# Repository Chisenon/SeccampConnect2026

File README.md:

# SeccampConnect2026
Security Camp Connect 2026

## クイックスタート（開発・書き込み手順）

開発には Docker (ビルド用) とホスト側の `espflash` (書き込み用) を使用します。
アーキテクチャの図解やコマンドの詳細は [WORKFLOW.md](WORKFLOW.md) を参照してください。

### 1. 開発用コンテナの起動
バックグラウンドでビルド用コンテナを待機させます。
```powershell
docker compose up -d
```

### 2. ビルドの実行
起動中のコンテナ内で `cargo build` を実行します。
```powershell
docker compose exec build cargo build --release
```

### 3. デバイスを「書き込みモード」にする（重要！）
ESP32-S3に書き込むには、マイコンを**ダウンロードモード**にする必要があります。

1. マイコン基板上の **BOOTボタン** を押しっぱなしにする
2. PCにUSBケーブルを接続する（接続済みの場合は、BOOTを押しながらRESETボタンを押して離す）
3. BOOTボタンを離す

### 4. ファームウェアの書き込み
割り当てられたCOMポート（例：`COM3`）を確認して書き込みます。
```powershell
# ポート確認
Get-CimInstance Win32_SerialPort | Select-Object Name, Description

# フラッシュ（COM3の場合）
espflash flash .\target\xtensa-esp32s3-none-elf\release\SeccampConnect2026 --port COM3
```

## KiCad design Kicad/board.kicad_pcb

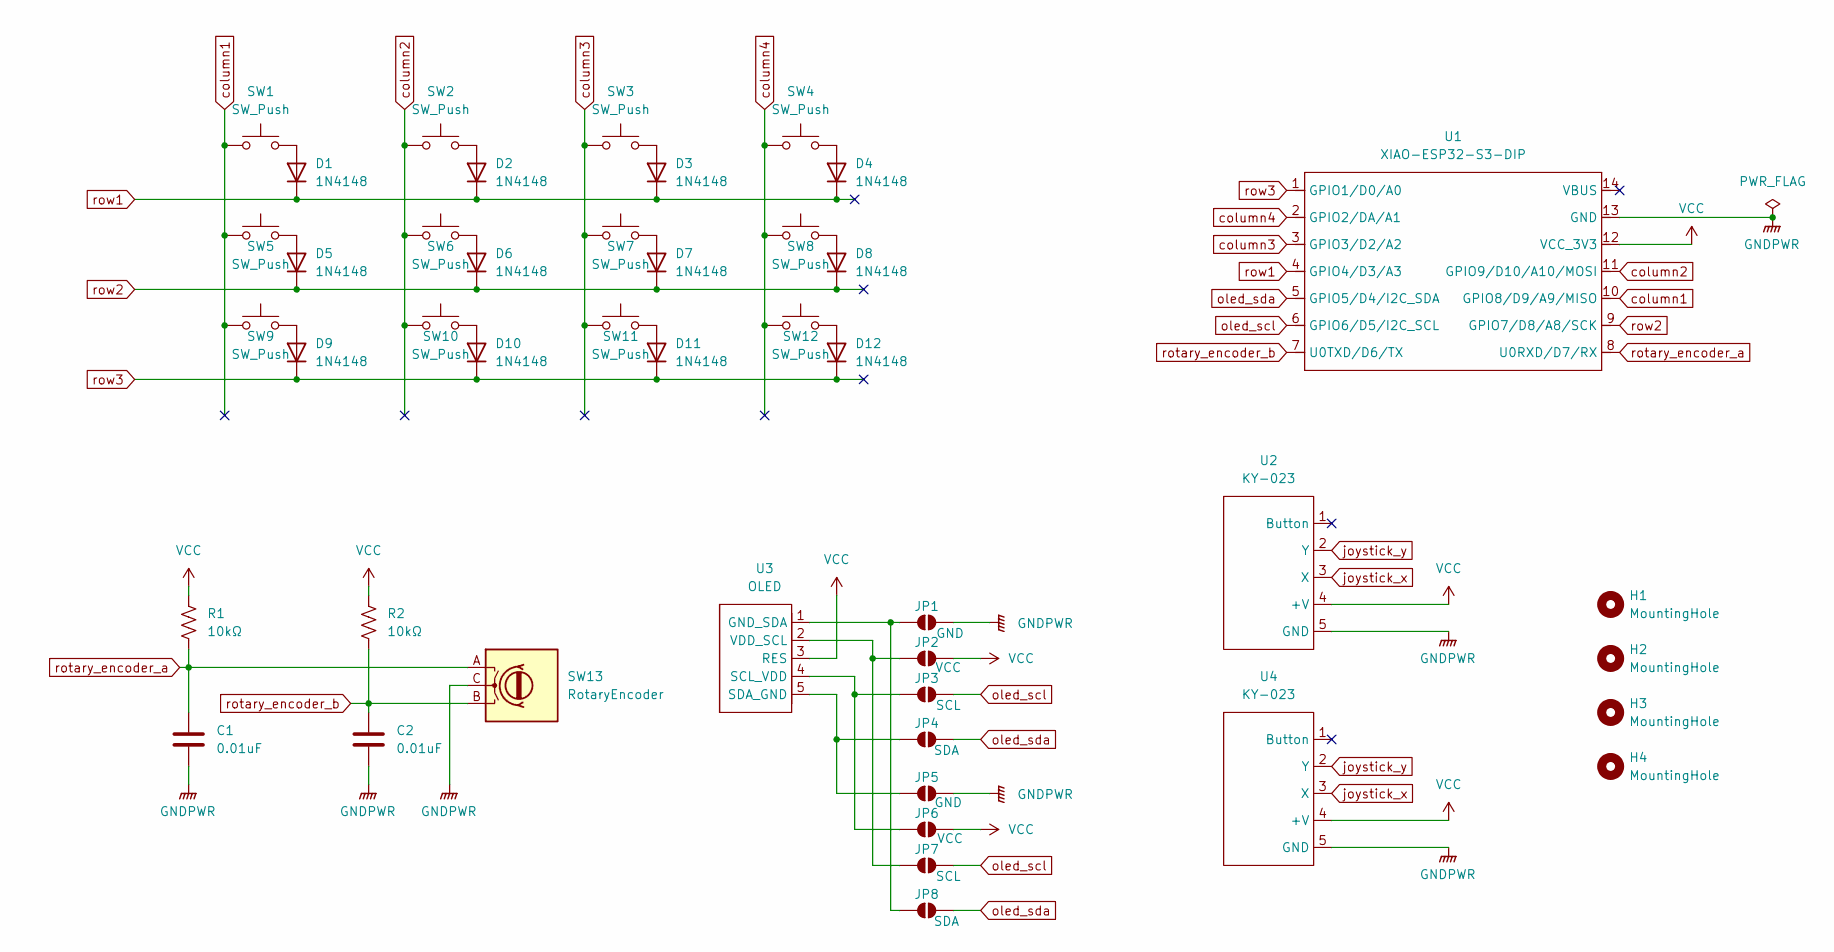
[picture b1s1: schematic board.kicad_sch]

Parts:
C1, C2: 0.01uF; C_0805_2012_HandSolder_reversible
D1, D2, D3, D4, D5, D6, D7, D8, D9, D10, D11, D12: 1N4148; Diode_THT_reversible
H1, H2, H3, H4: MountingHole; MountingHole_2.7mm
JP1, JP5: GND; SolderJumper-2_P1.3mm_Open_TrianglePad1.0x1.5mm
JP2, JP6: VCC; SolderJumper-2_P1.3mm_Open_TrianglePad1.0x1.5mm
JP3, JP7: SCL; SolderJumper-2_P1.3mm_Open_TrianglePad1.0x1.5mm
JP4, JP8: SDA; SolderJumper-2_P1.3mm_Open_TrianglePad1.0x1.5mm
R1, R2: 10kΩ; R_L6.3mm_D2.5mm_P10.16mm_Horizontal_reversible
SW1, SW2, SW3, SW4, SW5, SW6, SW7, SW8, SW9, SW10, SW11, SW12: SW_Push; Kailh_socket_PG1350_optional_reversible
SW13: RotaryEncoder; RotaryEncoder_Alps_EC12E_Vertical_H20mm
U1: XIAO-ESP32-S3-DIP; XIAO-ESP32S3_reversible
U2, U4: KY-023
U3: OLED; PinSocket_1x05_P2.54mm_Vertical

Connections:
GNDPWR: C1.2, C2.2, JP1.2 (B), JP5.2 (B), SW13.C, U1.13 (GND), U2.5 (GND), U4.5 (GND)
unnamed: D1.2 (A), SW1.2
unnamed: D2.2 (A), SW2.2
unnamed: D3.2 (A), SW3.2
unnamed: D4.2 (A), SW4.2
unnamed: D5.2 (A), SW5.2
unnamed: D6.2 (A), SW6.2
unnamed: D7.2 (A), SW7.2
unnamed: D8.2 (A), SW8.2
unnamed: D9.2 (A), SW9.2
unnamed: D10.2 (A), SW10.2
unnamed: D11.2 (A), SW11.2
unnamed: D12.2 (A), SW12.2
unnamed: JP1.1 (A), JP8.1 (A), U3.1 (GND_SDA)
unnamed: JP2.1 (A), JP7.1 (A), U3.2 (VDD_SCL)
unnamed: JP3.1 (A), JP6.1 (A), U3.4 (SCL_VDD)
unnamed: JP4.1 (A), JP5.1 (A), U3.5 (SDA_GND)
unnamed: U2.2 (Y), U4.2 (Y)
unnamed: U2.3 (X), U4.3 (X)
VCC: JP2.2 (B), JP6.2 (B), R1.1, R2.1, U1.12 (VCC_3V3), U2.4 (+V), U3.3 (RES), U4.4 (+V)
column1: SW1.1, SW5.1, SW9.1, U1.10 (GPIO8/D9/A9/MISO)
column2: SW2.1, SW6.1, SW10.1, U1.11 (GPIO9/D10/A10/MOSI)
column3: SW3.1, SW7.1, SW11.1, U1.3 (GPIO3/D2/A2)
column4: SW4.1, SW8.1, SW12.1, U1.2 (GPIO2/DA/A1)
oled_scl: JP3.2 (B), JP7.2 (B), U1.6 (GPIO6/D5/I2C_SCL)
oled_sda: JP4.2 (B), JP8.2 (B), U1.5 (GPIO5/D4/I2C_SDA)
rotary_encoder_a: C1.1, R1.2, SW13.A, U1.8 (U0RXD/D7/RX)
rotary_encoder_b: C2.1, R2.2, SW13.B, U1.7 (U0TXD/D6/TX)
row1: D1.1 (K), D2.1 (K), D3.1 (K), D4.1 (K), U1.4 (GPIO4/D3/A3)
row2: D5.1 (K), D6.1 (K), D7.1 (K), D8.1 (K), U1.9 (GPIO7/D8/A8/SCK)
row3: D9.1 (K), D10.1 (K), D11.1 (K), D12.1 (K), U1.1 (GPIO1/D0/A0)

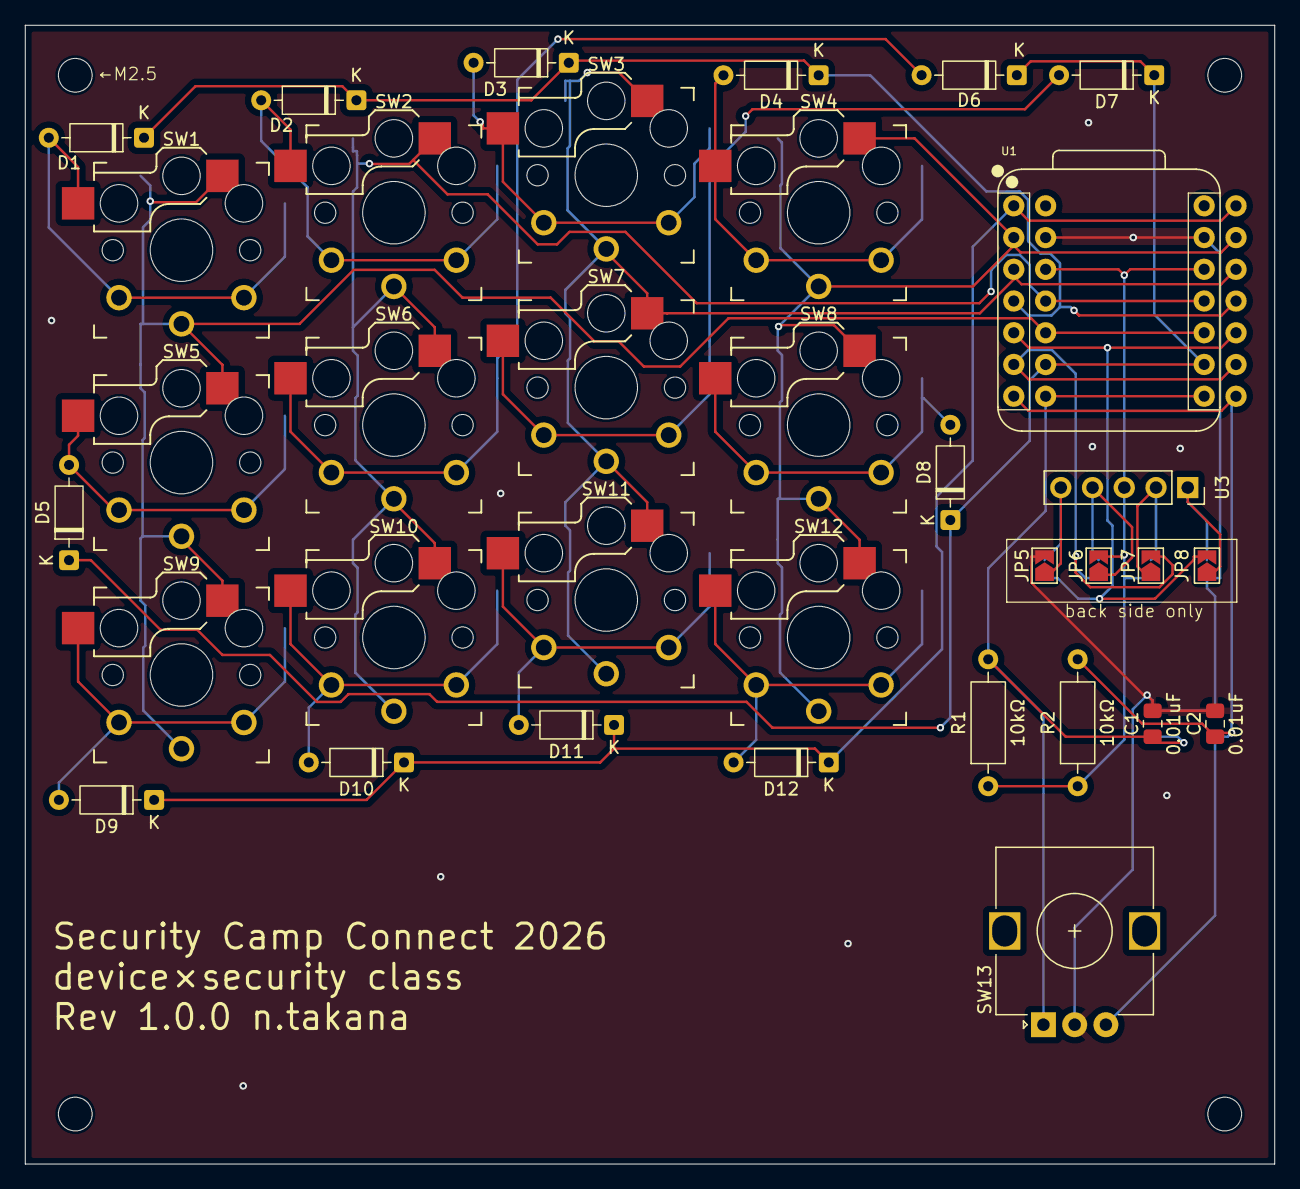
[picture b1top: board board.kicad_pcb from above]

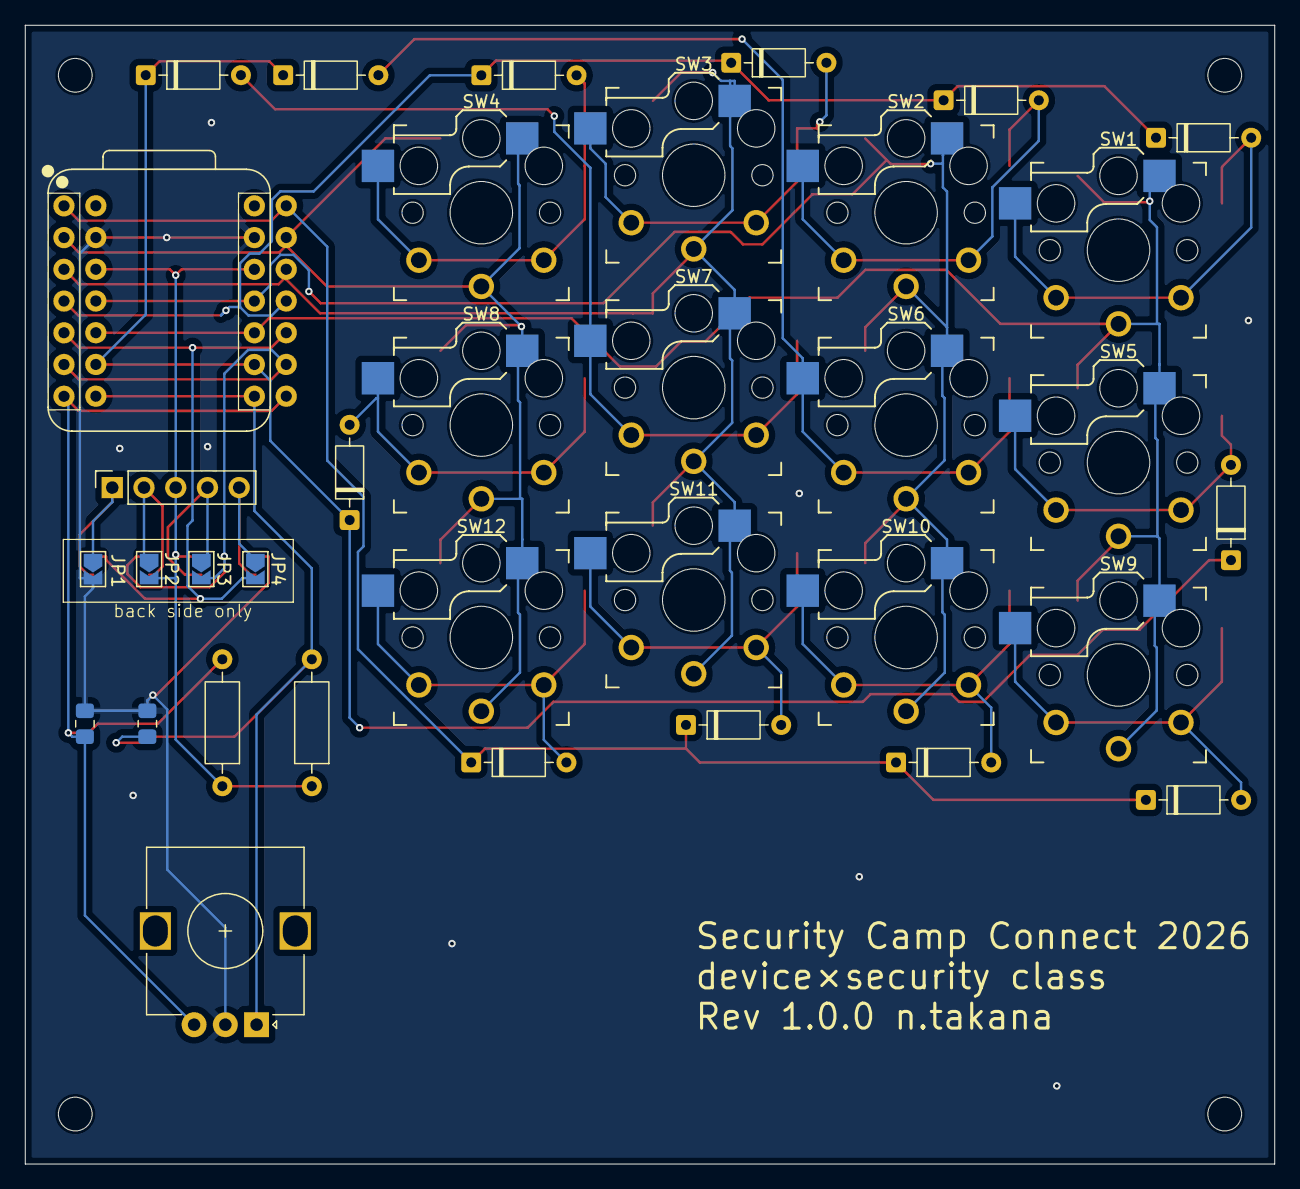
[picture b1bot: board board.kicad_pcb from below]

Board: 2 copper layers, 100.0 x 91.1 mm, 43 parts (4 on the bottom side), 29 nets.

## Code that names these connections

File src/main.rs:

//! Security Camp Connect 2026
//!
//! [https://www.ipa.go.jp/jinzai/security-camp/2025/connect/device.html](https://www.ipa.go.jp/jinzai/security-camp/2025/connect/device.html)
//!
//! 3x4 prototyping keyboards designed for hands-on practice.
//!
//! # Feature
//! - ESP32S3
//! - Vial support
//! - Low profile with 17 mm pitch
//! - Integrated rotary encoder and 0.91-inch OLED

#![no_std]
#![no_main]

mod keymap;
#[macro_use]
mod macros;
mod oled;
mod vial;

use core::ptr::addr_of_mut;

use bt_hci::controller::ExternalController;
use embassy_executor::Spawner;
use esp_hal::clock::CpuClock;
use esp_hal::gpio::{Input, InputConfig, Level, Output, OutputConfig, Pull};
use esp_hal::otg_fs::Usb;
use esp_hal::otg_fs::asynch::{Config, Driver};
use esp_hal::rng::TrngSource;
use esp_hal::timer::timg::TimerGroup;
use esp_radio::Controller;
use esp_radio::ble::controller::BleConnector;
use esp_storage::FlashStorage;
use rmk::ble::build_ble_stack;
use rmk::channel::EVENT_CHANNEL;
use rmk::config::{
    BehaviorConfig, DeviceConfig, PositionalConfig, RmkConfig, StorageConfig, VialConfig,
};
use rmk::debounce::default_debouncer::DefaultDebouncer;
use rmk::futures::future::join3;
use rmk::input_device::Runnable;
use rmk::input_device::rotary_encoder::DefaultPhase;
use rmk::input_device::rotary_encoder::RotaryEncoder;
use rmk::keyboard::Keyboard;
use rmk::matrix::Matrix;
use rmk::storage::async_flash_wrapper;
use rmk::{HostResources, initialize_encoder_keymap_and_storage, run_devices, run_rmk};
use ssd1306::prelude::DisplayRotation;
use static_cell::StaticCell;
use {esp_alloc as _, esp_backtrace as _};

use crate::keymap::{COL, ROW};
use crate::vial::{VIAL_KEYBOARD_DEF, VIAL_KEYBOARD_ID};

::esp_bootloader_esp_idf::esp_app_desc!();

/// Main function.
///
/// Initialize devices and spawn rmk tasks.
#[allow(clippy::used_underscore_binding)]
#[esp_rtos::main]
async fn main(spawner: Spawner) {
    // Singleton for ble controller.
    static RADIO: StaticCell<Controller<'static>> = StaticCell::new();
    // Endpoint buffer for USB transfer.
    static mut EP_MEMORY: [u8; 1024] = [0; 1024];

    // Initialize the peripherals and bluetooth controller
    esp_println::logger::init_logger_from_env();
    let peripherals = esp_hal::init(esp_hal::Config::default().with_cpu_clock(CpuClock::max()));
    esp_alloc::heap_allocator!(size: 72 * 1024);
    let timg0 = TimerGroup::new(peripherals.TIMG0);
    #[cfg(target_arch = "riscv32")]
    let software_interrupt = SoftwareInterruptControl::new(peripherals.SW_INTERRUPT);
    esp_rtos::start(
        timg0.timer0,
        #[cfg(target_arch = "riscv32")]
        software_interrupt.software_interrupt0,
    );
    let _trng_source = TrngSource::new(peripherals.RNG, peripherals.ADC1);
    let mut rng = esp_hal::rng::Trng::try_new().unwrap();
    let radio = RADIO.init(esp_radio::init().unwrap());
    let bluetooth = peripherals.BT;
    let connector = BleConnector::new(radio, bluetooth, esp_radio::ble::Config::default()).unwrap();
    let controller: ExternalController<_, 20> = ExternalController::new(connector);
    let central_addr = [0x18, 0xe2, 0x21, 0x80, 0xc0, 0xc7];
    let mut host_resources = HostResources::new();
    let stack = build_ble_stack(controller, central_addr, &mut rng, &mut host_resources).await;

    // Initialize USB
    let usb = Usb::new(peripherals.USB0, peripherals.GPIO20, peripherals.GPIO19);
    // Create the driver, from the HAL.
    let config = Config::default();
    let usb_driver = Driver::new(usb, unsafe { &mut *addr_of_mut!(EP_MEMORY) }, config);

    // Initialize the flash
    let flash = FlashStorage::new(peripherals.FLASH);
    let flash = async_flash_wrapper(flash);

    // Spawn oled task
    let display = oled::init_oled(
        peripherals.I2C0,
        peripherals.GPIO5,
        peripherals.GPIO6,
        DisplayRotation::Rotate0,
    )
    .await;
    if let Some(display) = display {
        spawner.spawn(oled::oled_task(display)).unwrap();
    }

    // Initialize the IO pins
    let (row_pins, col_pins) = config_matrix_pins_esp!(peripherals: peripherals, input: [GPIO4, GPIO7, GPIO1], output: [GPIO8, GPIO9, GPIO3, GPIO2]);

    // RMK config
    let vial_config = VialConfig::new(VIAL_KEYBOARD_ID, VIAL_KEYBOARD_DEF, &[(0, 0), (1, 1)]);
    let storage_config = StorageConfig {
        start_addr: 0x3f_0000,
        num_sectors: 16,
        ..Default::default()
    };
    let device_config = DeviceConfig {
        manufacturer: "RMK",
        product_name: "one Keyboard",
        ..Default::default()
    };
    let rmk_config = RmkConfig {
        vial_config,
        storage_config,
        device_config,
        ..Default::default()
    };

    // Initialze keyboard stuffs
    // Initialize the storage and keymap
    let mut default_keymap = keymap::get_default_keymap();
    let mut behavior_config = BehaviorConfig::default();
    let mut encoder_map = keymap::get_default_encoder_map();
    let mut per_key_config = PositionalConfig::default();
    let (keymap, mut storage) = initialize_encoder_keymap_and_storage(
        &mut default_keymap,
        &mut encoder_map,
        flash,
        &storage_config,
        &mut behavior_config,
        &mut per_key_config,
    )
    .await;

    // Initialize the matrix and keyboard
    let debouncer = DefaultDebouncer::new();
    let mut matrix = Matrix::<_, _, _, ROW, COL, true>::new(row_pins, col_pins, debouncer);
    let mut keyboard = Keyboard::new(&keymap); // Initialize the light controller

    // Initialize rotary encoder
    let pin_a = Input::new(peripherals.GPIO43, InputConfig::default());
    let pin_b = Input::new(peripherals.GPIO44, InputConfig::default());
    let mut encoder = RotaryEncoder::with_phase(pin_a, pin_b, DefaultPhase, 0);

    join3(
        run_devices! (
            (matrix, encoder) => EVENT_CHANNEL,
        ),
        keyboard.run(), // Keyboard is special
        run_rmk(&keymap, usb_driver, &stack, &mut storage, rmk_config),
    )
    .await;
}

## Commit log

2026-03-26 [fix] update Dockerfile and docker-compose.yml for non-root user support; enhance build scripts
2026-03-27 [docs] update README and WORKFLOW for improved development instructions and clarity
2026-03-27 [fix] update OLED display task to handle optional display initialization; improve display management
2026-03-28 [Update] product name in DeviceConfig from "my Keyboard" to "one Keyboard"
